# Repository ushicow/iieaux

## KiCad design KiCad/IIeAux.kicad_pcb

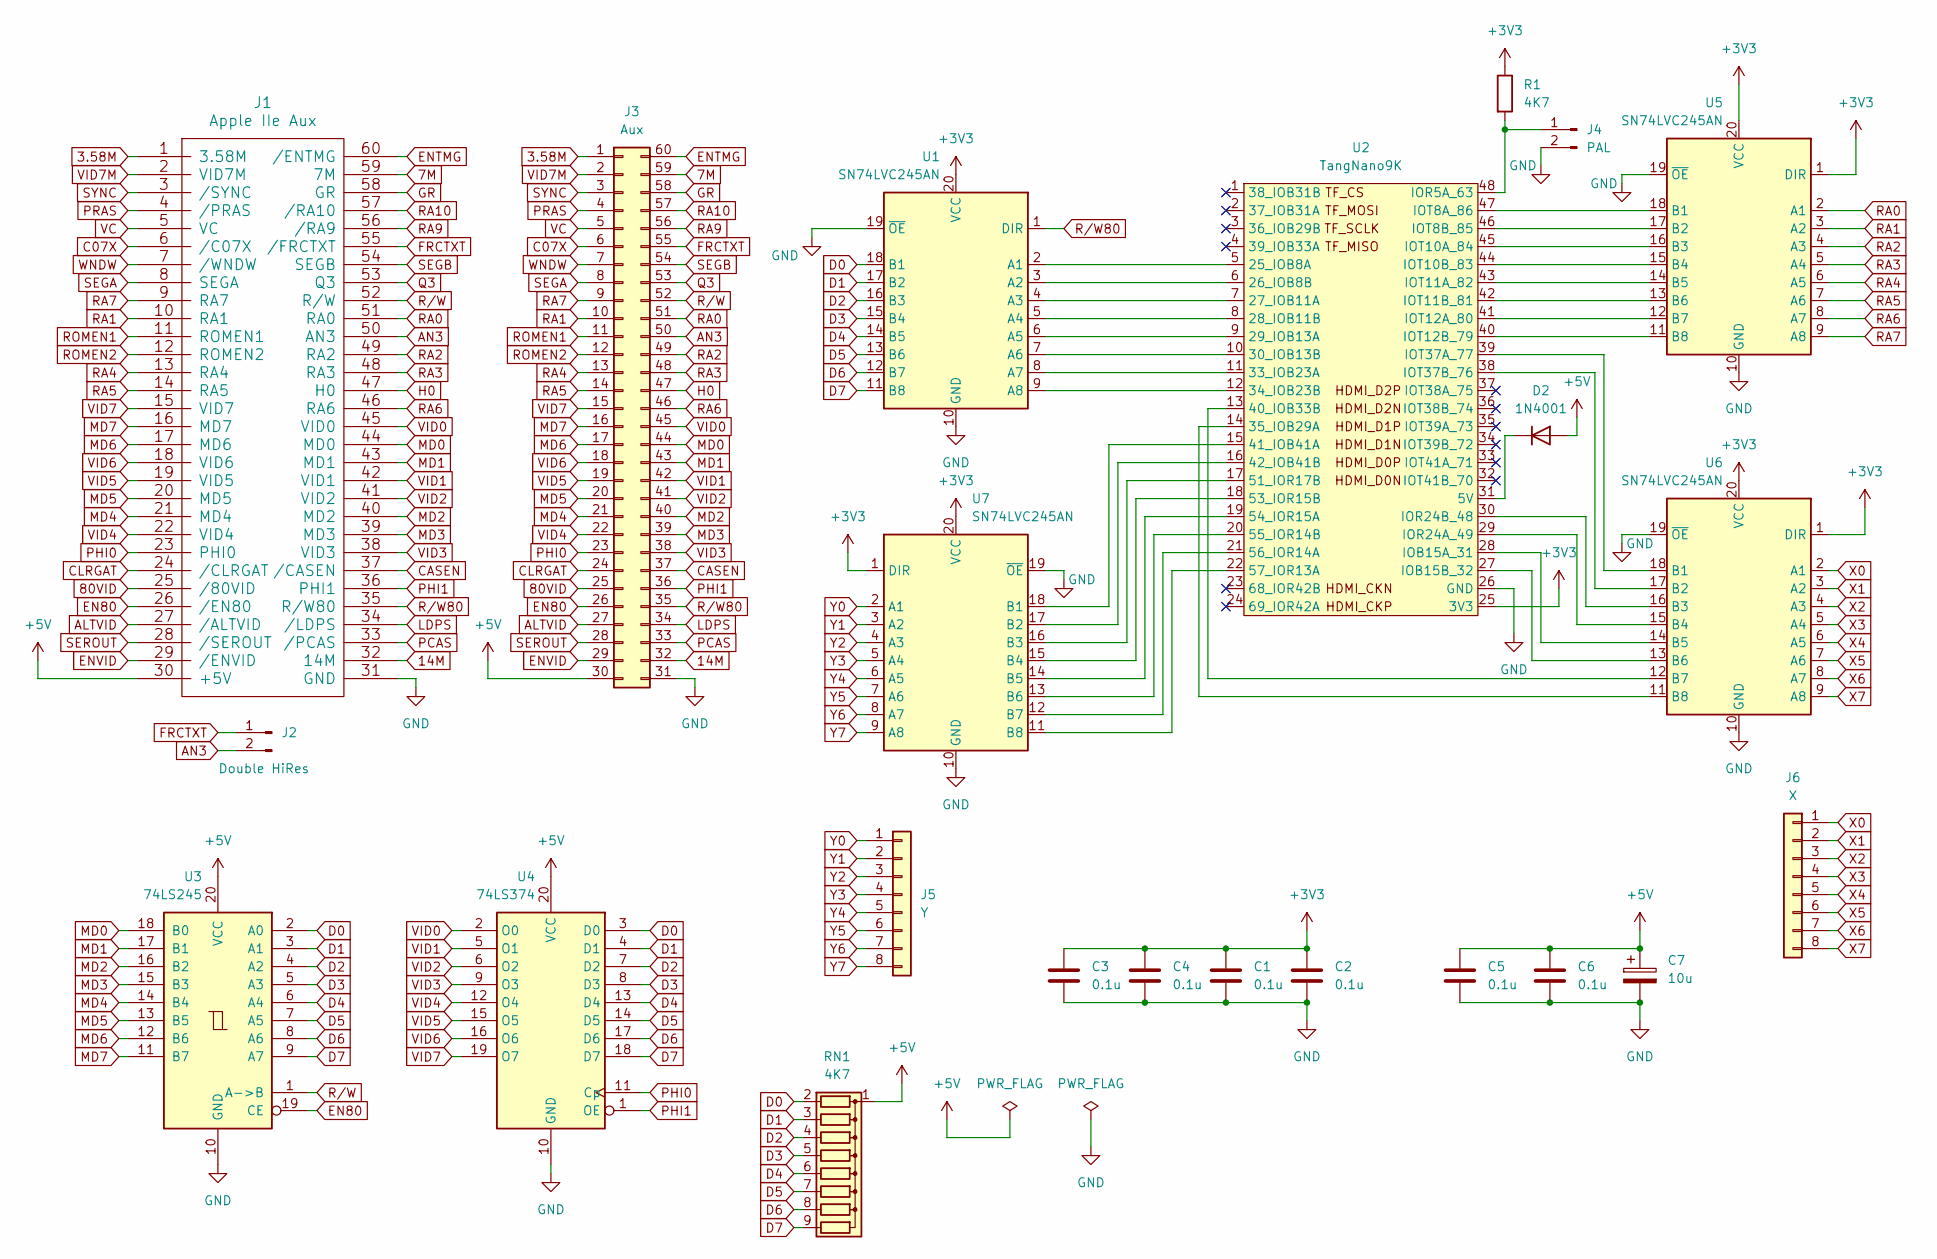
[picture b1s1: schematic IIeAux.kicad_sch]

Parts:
C1, C2, C3, C4, C5, C6: 0.1u; C_Disc_D4.3mm_W1.9mm_P5.08mm
C7: 10u; CP_Radial_D5.0mm_P2.00mm
D2: 1N4001; D_DO-41_SOD81_P10.16mm_Horizontal
J1: Apple IIe Aux; IIE_Aux
J2: Double HiRes; PinHeader_1x02_P2.54mm_Horizontal
J3: Aux; PinSocket_2x30_P2.54mm
J4: PAL; PinHeader_1x02_P2.54mm_Horizontal
J5: Y; PinSocket_1x08_P2.54mm_Vertical
J6: X; PinSocket_1x08_P2.54mm_Vertical
R1: 4K7; R_Axial_DIN0207_L6.3mm_D2.5mm_P10.16mm_Horizontal
RN1: 4K7; R_Array_SIP9
U1, U5, U6, U7: SN74LVC245AN; DIP-20_W7.62mm
U2: TangNano9K
U3: 74LS245; DIP-20_W7.62mm_Socket
U4: 74LS374; DIP-20_W7.62mm_Socket

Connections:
3.58M: J1.1 (3.58M), J3.1
7M: J1.59 (7M), J3.59
14M: J1.32 (14M), J3.32
80VID: J1.25 (/80VID), J3.25
+3V3: C1.1, C2.1, C3.1, C4.1, R1.1, U1.20 (VCC), U2.25 (3V3), U5.1 (DIR), U5.20 (VCC), U6.1 (DIR), U6.20 (VCC), U7.1 (DIR), U7.20 (VCC)
+5V: C5.1, C6.1, C7.1, D2.2 (A), J1.30 (+5V), J3.30, RN1.1 (common), U3.20 (VCC), U4.20 (VCC)
ALTVID: J1.27 (/ALTVID), J3.27
AN3: J1.50 (AN3), J2.2, J3.50
C07X: J1.6 (/C07X), J3.6
CASEN: J1.37 (/CASEN), J3.37
CLRGAT: J1.24 (/CLRGAT), J3.24
D0: RN1.2 (R1), U1.18 (B1), U3.2 (A0), U4.3 (D0)
D1: RN1.3 (R2), U1.17 (B2), U3.3 (A1), U4.4 (D1)
D2: RN1.4 (R3), U1.16 (B3), U3.4 (A2), U4.7 (D2)
D3: RN1.5 (R4), U1.15 (B4), U3.5 (A3), U4.8 (D3)
D4: RN1.6 (R5), U1.14 (B5), U3.6 (A4), U4.13 (D4)
D5: RN1.7 (R6), U1.13 (B6), U3.7 (A5), U4.14 (D5)
D6: RN1.8 (R7), U1.12 (B7), U3.8 (A6), U4.17 (D6)
D7: RN1.9 (R8), U1.11 (B8), U3.9 (A7), U4.18 (D7)
EN80: J1.26 (/EN80), J3.26, U3.19 (CE)
ENTMG: J1.60 (/ENTMG), J3.60
ENVID: J1.29 (/ENVID), J3.29
FRCTXT: J1.55 (/FRCTXT), J2.1, J3.55
GND: C1.2, C2.2, C3.2, C4.2, C5.2, C6.2, C7.2, J1.31 (GND), J3.31, J4.2, U1.10 (GND), U1.19 (~OE), U2.26 (GND), U3.10 (GND), U4.10 (GND), U5.10 (GND), U5.19 (~OE), U6.10 (GND), U6.19 (~OE), U7.10 (GND), U7.19 (~OE)
GR: J1.58 (GR), J3.58
H0: J1.47 (H0), J3.47
LDPS: J1.34 (/LDPS), J3.34
MD0: J1.44 (MD0), J3.44, U3.18 (B0)
MD1: J1.43 (MD1), J3.43, U3.17 (B1)
MD2: J1.40 (MD2), J3.40, U3.16 (B2)
MD3: J1.39 (MD3), J3.39, U3.15 (B3)
MD4: J1.21 (MD4), J3.21, U3.14 (B4)
MD5: J1.20 (MD5), J3.20, U3.13 (B5)
MD6: J1.17 (MD6), J3.17, U3.12 (B6)
MD7: J1.16 (MD7), J3.16, U3.11 (B7)
unnamed: D2.1 (K), U2.31 (5V)
unnamed: J4.1, R1.2, U2.48 (IOR5A_63)
unnamed: U1.2 (A1), U2.5 (25_IOB8A)
unnamed: U1.3 (A2), U2.6 (26_IOB8B)
unnamed: U1.4 (A3), U2.7 (27_IOB11A)
unnamed: U1.5 (A4), U2.8 (28_IOB11B)
unnamed: U1.6 (A5), U2.9 (29_IOB13A)
unnamed: U1.7 (A6), U2.10 (30_IOB13B)
unnamed: U1.8 (A7), U2.11 (33_IOB23A)
unnamed: U1.9 (A8), U2.12 (34_IOB23B)
unnamed: U2.14 (35_IOB29A), U6.11 (B8)
unnamed: U2.13 (40_IOB33B), U6.12 (B7)
unnamed: U2.15 (41_IOB41A), U7.18 (B1)
unnamed: U2.16 (42_IOB41B), U7.17 (B2)
unnamed: U2.17 (51_IOR17B), U7.16 (B3)
unnamed: U2.18 (53_IOR15B), U7.15 (B4)
unnamed: U2.19 (54_IOR15A), U7.14 (B5)
unnamed: U2.20 (55_IOR14B), U7.13 (B6)
unnamed: U2.21 (56_IOR14A), U7.12 (B7)
unnamed: U2.22 (57_IOR13A), U7.11 (B8)
unnamed: U2.28 (IOB15A_31), U6.14 (B5)
unnamed: U2.27 (IOB15B_32), U6.13 (B6)
unnamed: U2.29 (IOR24A_49), U6.15 (B4)
unnamed: U2.30 (IOR24B_48), U6.16 (B3)
unnamed: U2.47 (IOT8A_86), U5.18 (B1)
unnamed: U2.46 (IOT8B_85), U5.17 (B2)
unnamed: U2.45 (IOT10A_84), U5.16 (B3)
unnamed: U2.44 (IOT10B_83), U5.15 (B4)
unnamed: U2.43 (IOT11A_82), U5.14 (B5)
unnamed: U2.42 (IOT11B_81), U5.13 (B6)
unnamed: U2.41 (IOT12A_80), U5.12 (B7)
unnamed: U2.40 (IOT12B_79), U5.11 (B8)
unnamed: U2.39 (IOT37A_77), U6.18 (B1)
unnamed: U2.38 (IOT37B_76), U6.17 (B2)
PCAS: J1.33 (/PCAS), J3.33
PHI0: J1.23 (PHI0), J3.23, U4.11 (Cp)
PHI1: J1.36 (PHI1), J3.36, U4.1 (OE)
PRAS: J1.4 (/PRAS), J3.4
Q3: J1.53 (Q3), J3.53
RA0: J1.51 (RA0), J3.51, U5.2 (A1)
RA1: J1.10 (RA1), J3.10, U5.3 (A2)
RA2: J1.49 (RA2), J3.49, U5.4 (A3)
RA3: J1.48 (RA3), J3.48, U5.5 (A4)
RA4: J1.13 (RA4), J3.13, U5.6 (A5)
RA5: J1.14 (RA5), J3.14, U5.7 (A6)
RA6: J1.46 (RA6), J3.46, U5.8 (A7)
RA7: J1.9 (RA7), J3.9, U5.9 (A8)
RA9: J1.56 (/RA9), J3.56
RA10: J1.57 (/RA10), J3.57
ROMEN1: J1.11 (ROMEN1), J3.11
ROMEN2: J1.12 (ROMEN2), J3.12
R/W: J1.52 (R/W), J3.52, U3.1 (A->B)
R/W80: J1.35 (R/W80), J3.35, U1.1 (DIR)
SEGA: J1.8 (SEGA), J3.8
SEGB: J1.54 (SEGB), J3.54
SEROUT: J1.28 (/SEROUT), J3.28
SYNC: J1.3 (/SYNC), J3.3
VC: J1.5 (VC), J3.5
VID0: J1.45 (VID0), J3.45, U4.2 (O0)
VID1: J1.42 (VID1), J3.42, U4.5 (O1)
VID2: J1.41 (VID2), J3.41, U4.6 (O2)
VID3: J1.38 (VID3), J3.38, U4.9 (O3)
VID4: J1.22 (VID4), J3.22, U4.12 (O4)
VID5: J1.19 (VID5), J3.19, U4.15 (O5)
VID6: J1.18 (VID6), J3.18, U4.16 (O6)
VID7: J1.15 (VID7), J3.15, U4.19 (O7)
VID7M: J1.2 (VID7M), J3.2
WNDW: J1.7 (/WNDW), J3.7
X0: J6.1, U6.2 (A1)
X1: J6.2, U6.3 (A2)
X2: J6.3, U6.4 (A3)
X3: J6.4, U6.5 (A4)
X4: J6.5, U6.6 (A5)
X5: J6.6, U6.7 (A6)
X6: J6.7, U6.8 (A7)
X7: J6.8, U6.9 (A8)
Y0: J5.1, U7.2 (A1)
Y1: J5.2, U7.3 (A2)
Y2: J5.3, U7.4 (A3)
Y3: J5.4, U7.5 (A4)
Y4: J5.5, U7.6 (A5)
Y5: J5.6, U7.7 (A6)
Y6: J5.7, U7.8 (A7)
Y7: J5.8, U7.9 (A8)

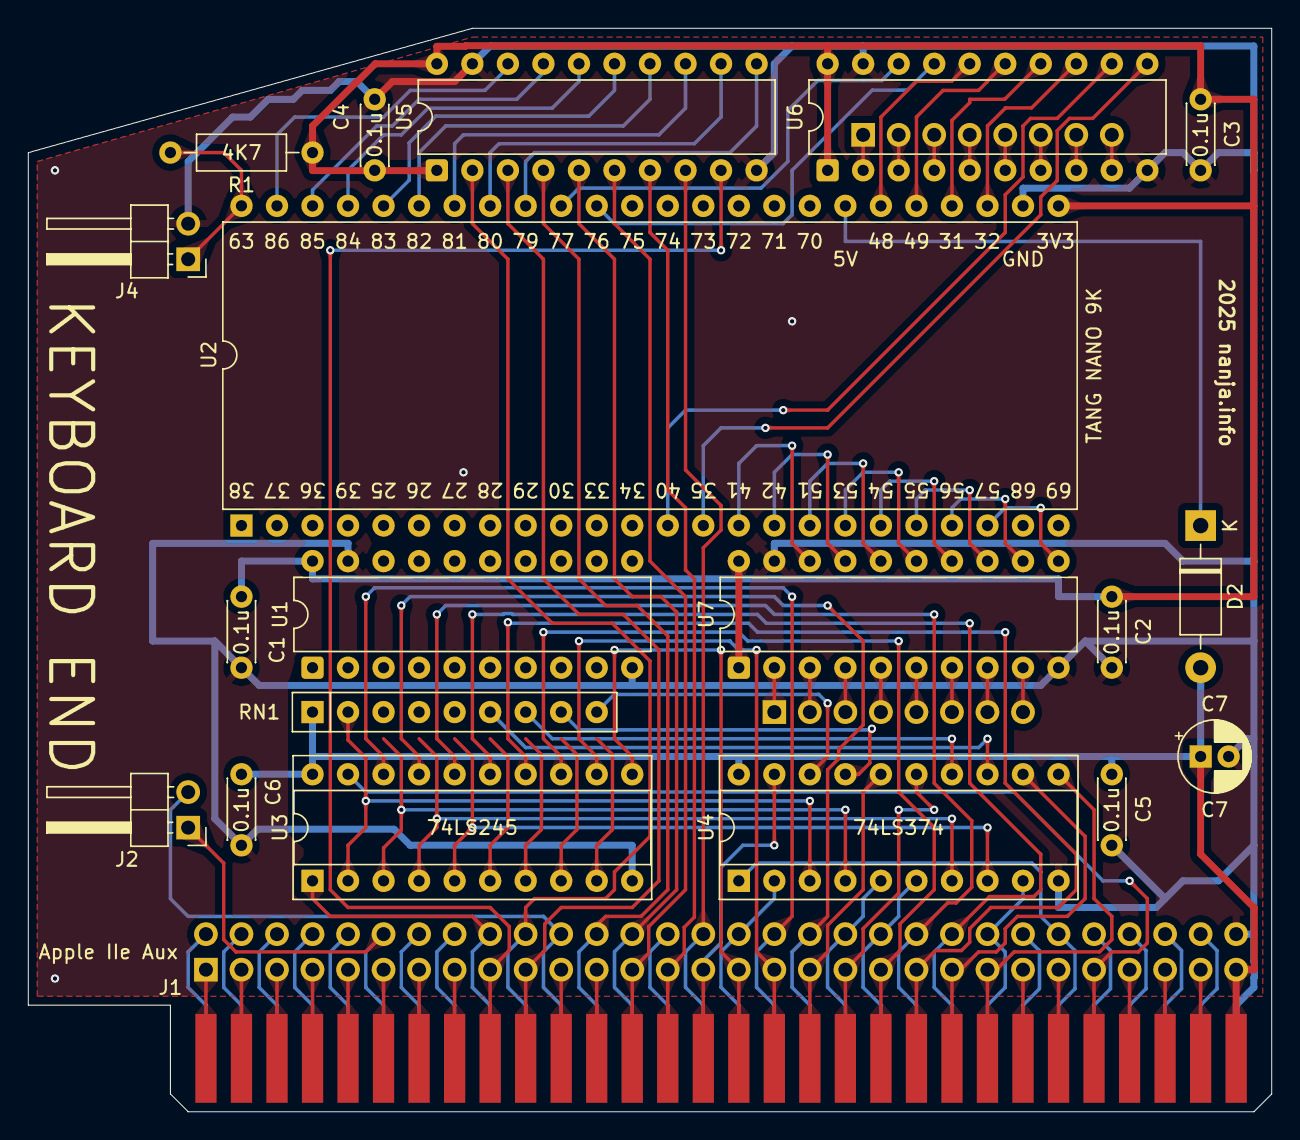
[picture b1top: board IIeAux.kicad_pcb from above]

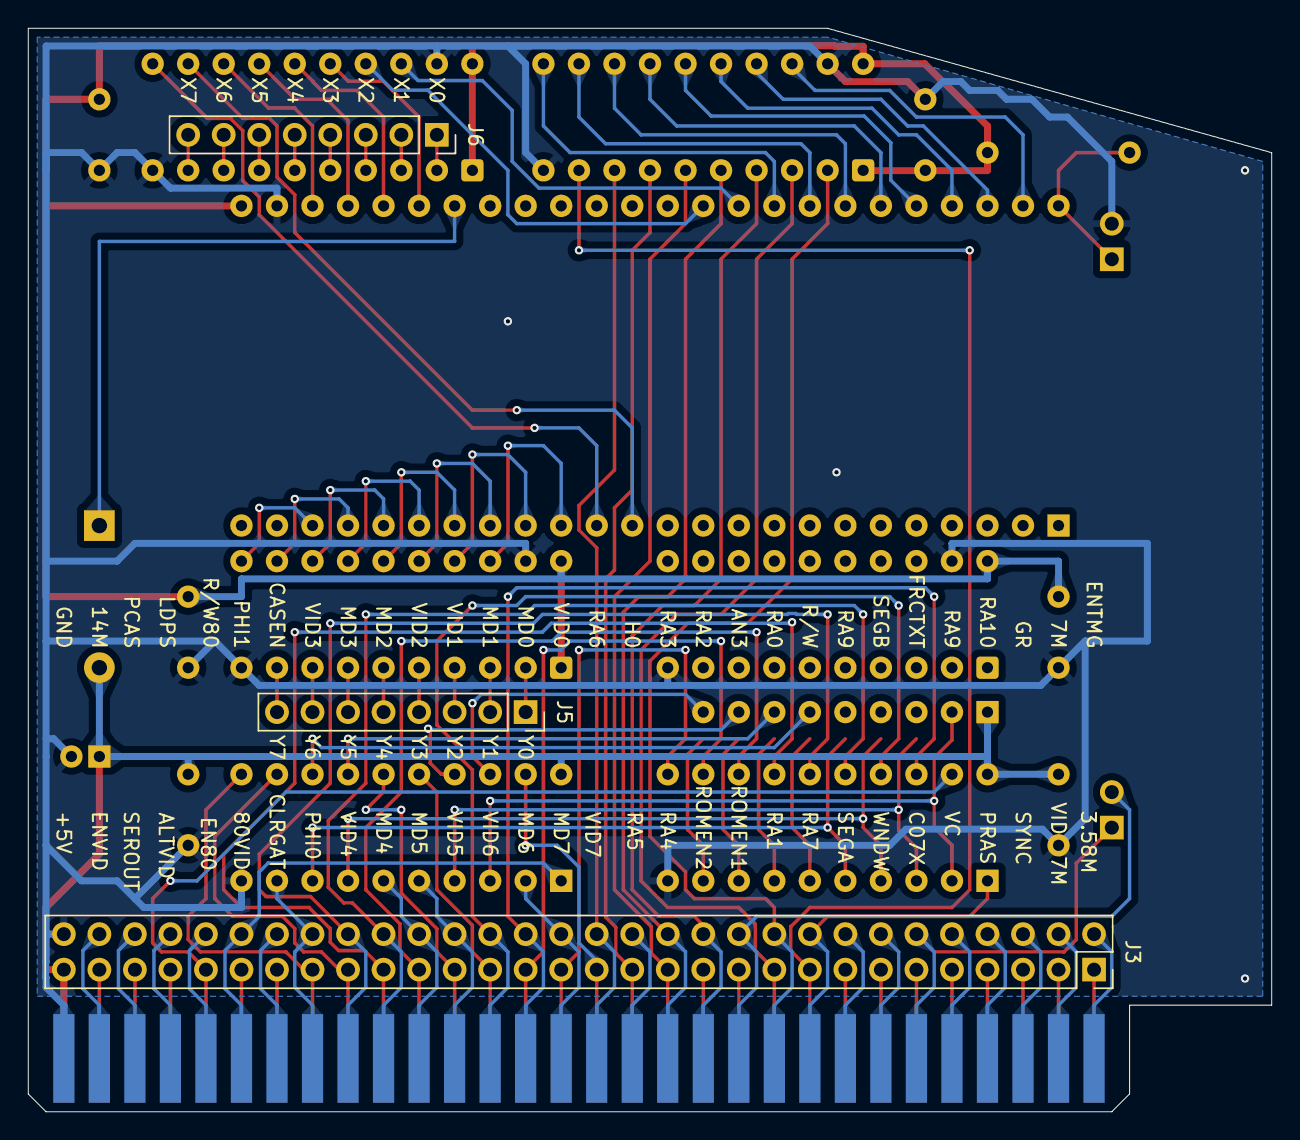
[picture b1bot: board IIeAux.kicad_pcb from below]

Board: 2 copper layers, 88.9 x 77.5 mm, 23 parts (3 on the bottom side), 119 nets.

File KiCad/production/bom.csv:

Designator,Footprint,Quantity,Value,LCSC Part #
"C1, C2, C3, C4, C5, C6",C_Disc_D4.3mm_W1.9mm_P5.08mm,6,0.1u,
C7,CP_Radial_D5.0mm_P2.00mm,1,10u,
D2,D_DO-41_SOD81_P10.16mm_Horizontal,1,1N4001,
J1,IIE_Aux,1,Apple IIe Aux,
J2,PinHeader_1x02_P2.54mm_Horizontal,1,Double HiRes,
J3,PinSocket_2x30_P2.54mm,1,Aux,
J4,PinHeader_1x02_P2.54mm_Horizontal,1,PAL,
J5,PinSocket_1x08_P2.54mm_Vertical,1,Y,
J6,PinSocket_1x08_P2.54mm_Vertical,1,X,
R1,R_Axial_DIN0207_L6.3mm_D2.5mm_P10.16mm_Horizontal,1,4K7,
RN1,R_Array_SIP9,1,4K7,
"U1, U5, U6, U7",DIP-20_W7.62mm,4,SN74LVC245AN,
U2,TangNano9K,1,TangNano9K,
U3,DIP-20_W7.62mm_Socket,1,74LS245,
U4,DIP-20_W7.62mm_Socket,1,74LS374,

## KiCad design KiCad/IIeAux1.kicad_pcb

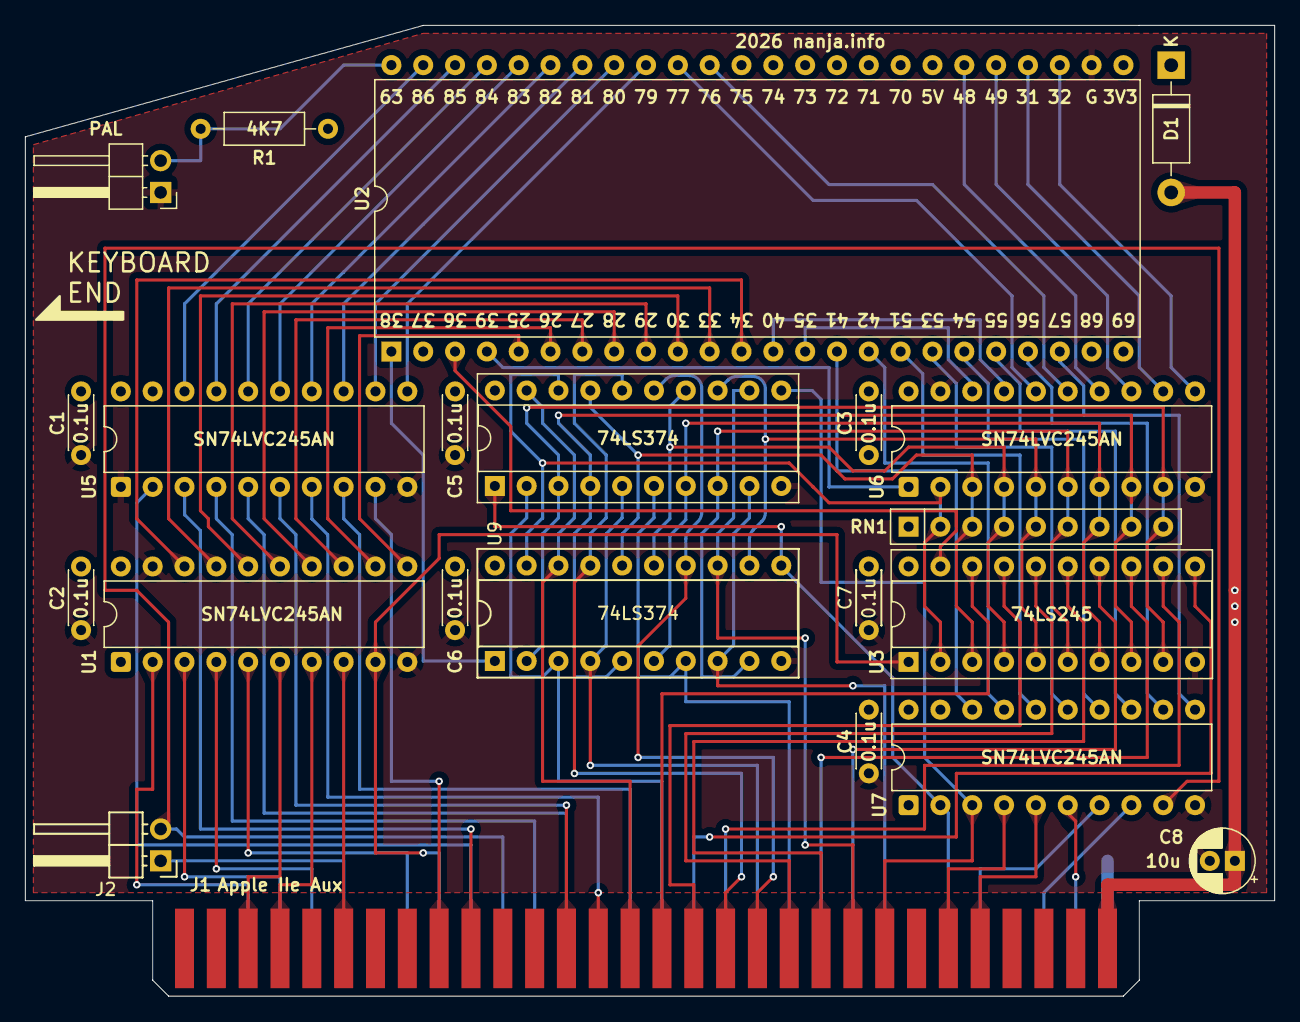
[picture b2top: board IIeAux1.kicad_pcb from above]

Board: 4 copper layers, 99.7 x 77.5 mm, 22 parts (0 on the bottom side), 89 nets.

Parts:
C1, C2, C3, C4, C5, C6, C7: 0.1u; C_Disc_D4.3mm_W1.9mm_P5.08mm
C8: 10u; CP_Radial_D5.0mm_P2.00mm
D1: 1N4001; D_DO-41_SOD81_P10.16mm_Horizontal
J1: Apple IIe Aux; IIE_Aux
J2: Double Hi-Res; PinHeader_1x02_P2.54mm_Horizontal
J3: PAL; PinHeader_1x02_P2.54mm_Horizontal
R1: 4K7; R_Axial_DIN0207_L6.3mm_D2.5mm_P10.16mm_Horizontal
RN1: 4K7; R_Array_SIP9
U1, U5, U6, U7: SN74LVC245AN; DIP-20_W7.62mm
U2: TangNano9K
U3: 74LS245; DIP-20_W7.62mm_Socket
U4, U9: 74LS374; DIP-20_W7.62mm_Socket

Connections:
14M: J1.32 (14M), U7.6 (A5)
80VID: J1.25 (/80VID), U7.4 (A3)
+3V3: C1.1, C2.1, C3.1, C4.1, R1.1, U1.1 (DIR), U1.20 (VCC), U2.25 (3V3), U5.20 (VCC), U6.20 (VCC), U7.1 (DIR), U7.20 (VCC)
+5V: C5.1, C6.1, C7.1, C8.1, D1.2 (A), J1.30 (+5V), RN1.1 (common), U3.20 (VCC), U4.20 (VCC), U9.20 (VCC)
AN3: J1.50 (AN3), J2.2, U7.9 (A8)
C07X: J1.6 (/C07X), U1.8 (A7)
D0: RN1.9 (R8), U3.9 (A7), U4.3 (D0), U6.9 (A8), U9.2 (O0)
D1: RN1.8 (R7), U3.8 (A6), U4.4 (D1), U6.8 (A7), U9.5 (O1)
D2: RN1.7 (R6), U3.7 (A5), U4.7 (D2), U6.7 (A6), U9.6 (O2)
D3: RN1.6 (R5), U3.6 (A4), U4.8 (D3), U6.6 (A5), U9.9 (O3)
D4: RN1.5 (R4), U3.5 (A3), U4.13 (D4), U6.5 (A4), U9.12 (O4)
D5: RN1.4 (R3), U3.4 (A2), U4.14 (D5), U6.4 (A3), U9.15 (O5)
D6: RN1.3 (R2), U3.3 (A1), U4.17 (D6), U6.3 (A2), U9.16 (O6)
D7: RN1.2 (R1), U3.2 (A0), U4.18 (D7), U6.2 (A1), U9.19 (O7)
D_RW: U2.4 (39_IOB33A), U6.1 (DIR)
EN80: J1.26 (/EN80), U7.5 (A4)
FRCTXT: J1.55 (/FRCTXT), J2.1
GND: C1.2, C2.2, C3.2, C4.2, C5.2, C6.2, C7.2, C8.2, J1.31 (GND), J3.1, U1.10 (GND), U1.19 (~OE), U2.26 (GND), U3.10 (GND), U4.10 (GND), U5.1 (DIR), U5.10 (GND), U5.19 (~OE), U6.10 (GND), U6.19 (~OE), U7.10 (GND), U7.19 (~OE), U9.10 (GND)
GR: J1.58 (GR), U1.2 (A1)
MD0: J1.44 (MD0), U3.11 (B7)
MD1: J1.43 (MD1), U3.12 (B6)
MD2: J1.40 (MD2), U3.13 (B5)
MD3: J1.39 (MD3), U3.14 (B4)
MD4: J1.21 (MD4), U3.15 (B3)
MD5: J1.20 (MD5), U3.16 (B2)
MD6: J1.17 (MD6), U3.17 (B1)
MD7: J1.16 (MD7), U3.18 (B0)
MD_EN: U2.3 (36_IOB29B), U3.19 (CE)
unnamed: D1.1 (K), U2.31 (5V)
unnamed: J3.2, R1.2, U2.48 (IOR5A_63)
unnamed: U1.18 (B1), U2.12 (34_IOB23B)
unnamed: U1.17 (B2), U2.11 (33_IOB23A)
unnamed: U1.16 (B3), U2.10 (30_IOB13B)
unnamed: U1.15 (B4), U2.9 (29_IOB13A)
unnamed: U1.14 (B5), U2.8 (28_IOB11B)
unnamed: U1.13 (B6), U2.7 (27_IOB11A)
unnamed: U1.12 (B7), U2.6 (26_IOB8B)
unnamed: U1.11 (B8), U2.5 (25_IOB8A)
unnamed: U2.14 (35_IOB29A), U6.18 (B1)
unnamed: U2.13 (40_IOB33B), U6.17 (B2)
unnamed: U2.15 (41_IOB41A), U7.18 (B1)
unnamed: U2.16 (42_IOB41B), U7.17 (B2)
unnamed: U2.17 (51_IOR17B), U7.16 (B3)
unnamed: U2.18 (53_IOR15B), U7.15 (B4)
unnamed: U2.19 (54_IOR15A), U7.14 (B5)
unnamed: U2.20 (55_IOR14B), U7.13 (B6)
unnamed: U2.21 (56_IOR14A), U7.12 (B7)
unnamed: U2.22 (57_IOR13A), U7.11 (B8)
unnamed: U2.28 (IOB15A_31), U6.12 (B7)
unnamed: U2.27 (IOB15B_32), U6.11 (B8)
unnamed: U2.29 (IOR24A_49), U6.13 (B6)
unnamed: U2.30 (IOR24B_48), U6.14 (B5)
unnamed: U2.47 (IOT8A_86), U5.18 (B1)
unnamed: U2.46 (IOT8B_85), U5.17 (B2)
unnamed: U2.45 (IOT10A_84), U5.16 (B3)
unnamed: U2.44 (IOT10B_83), U5.15 (B4)
unnamed: U2.43 (IOT11A_82), U5.14 (B5)
unnamed: U2.42 (IOT11B_81), U5.13 (B6)
unnamed: U2.41 (IOT12A_80), U5.12 (B7)
unnamed: U2.40 (IOT12B_79), U5.11 (B8)
unnamed: U2.39 (IOT37A_77), U6.16 (B3)
unnamed: U2.38 (IOT37B_76), U6.15 (B4)
PCAS: J1.33 (/PCAS), U7.8 (A7)
PHI0: J1.23 (PHI0), U4.11 (Cp), U7.3 (A2)
PHI1: J1.36 (PHI1), U4.1 (OE), U7.2 (A1), U9.11 (Cp)
PRAS: J1.4 (/PRAS), U1.7 (A6)
Q3: J1.53 (Q3), U1.5 (A4)
RA0: J1.51 (RA0), U5.2 (A1)
RA1: J1.10 (RA1), U5.3 (A2)
RA2: J1.49 (RA2), U5.4 (A3)
RA3: J1.48 (RA3), U5.5 (A4)
RA4: J1.13 (RA4), U5.6 (A5)
RA5: J1.14 (RA5), U5.7 (A6)
RA6: J1.46 (RA6), U5.8 (A7)
RA7: J1.9 (RA7), U5.9 (A8)
RA9: J1.56 (/RA9), U1.4 (A3)
RA10: J1.57 (/RA10), U1.3 (A2)
R/W: J1.52 (R/W), U1.9 (A8), U3.1 (A->B)
R/W80: J1.35 (R/W80), U7.7 (A6)
SYNC: J1.3 (/SYNC), U1.6 (A5)
VID0: J1.45 (VID0), U4.2 (O0), U9.3 (D0)
VID1: J1.42 (VID1), U4.5 (O1), U9.4 (D1)
VID2: J1.41 (VID2), U4.6 (O2), U9.7 (D2)
VID3: J1.38 (VID3), U4.9 (O3), U9.8 (D3)
VID4: J1.22 (VID4), U4.12 (O4), U9.13 (D4)
VID5: J1.19 (VID5), U4.15 (O5), U9.14 (D5)
VID6: J1.18 (VID6), U4.16 (O6), U9.17 (D6)
VID7: J1.15 (VID7), U4.19 (O7), U9.18 (D7)
VID_RD: U2.1 (38_IOB31B), U9.1 (OE)

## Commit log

2026-02-15 init
2026-03-03 PCB V1.1
2026-03-06 Use SEROUT signal
2026-03-07 V1.0 first batch
2026-03-07 fixed U1 direction
2026-03-07 80 Colmun Text
2026-03-11 DVI output 560 x 192
2026-03-14 VGA output test
2026-03-23 frame buffer
2026-03-28 extended 64K RAM
2026-03-29 color graphics
2026-04-05 modify byte R/W
2026-04-11 PSRAM clock 144MHz
2026-04-26 correct data bus timing
2026-05-01 PCB V2.0
2026-05-14 firmware for PCB V2.0
2026-05-16 4MB of RAM
2026-05-23 text color mode
2026-05-23 mono/color switch
